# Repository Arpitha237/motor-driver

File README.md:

# Dual DC Motor Driver (L293D) 

Controls two DC motors independently (direction & enable) using an L293D driver IC and a 5V regulated supply.

## Components:

* **U1 (L293D):** Dual H-bridge motor driver IC. This chip contains two independent H-bridge circuits, allowing control of the direction and current flow to two DC motors.
* **U2 (L7805):** 5V voltage regulator. This component takes a higher DC input voltage and provides a stable 5V output to power the L293D's logic and the indicator LED.
* **D1 (LED):** Light Emitting Diode. This visual indicator illuminates when the circuit has a stable 5V power supply.
* **R1 (Resistor):** Current-limiting resistor. This resistor is placed in series with the LED to prevent excessive current flow and potential damage to the LED.
* **J1 (Screw Terminal):** Input connector for the external DC power supply. This is where you connect your power source.
* **J2 (Header):** Connector for control input signals. This header receives signals (typically from a microcontroller) to control the enable and direction of both motors.
* **J3 (Header):** Connector for the first DC motor. Connect the two terminals of your first motor here.
* **J4 (Header):** Connector for the second DC motor. Connect the two terminals of your second motor here.

## Working:

1.  **Power Input:** External DC power is connected to the J1 screw terminal. Ensure correct polarity.
2.  **Voltage Regulation:** The L7805 (U2) steps down and stabilizes the input voltage to a consistent 5V, which is crucial for the proper operation of the L293D and other components.
3.  **Power Indication:** When the 5V regulation is successful, the LED (D1) lights up, indicating that the circuit is powered and ready for motor control.
4.  **Motor Enabling:** To allow a motor to run, a HIGH logic signal (+5V) must be applied to the corresponding enable pin on the J2 header (connected to the EN pins of U1). A LOW signal (0V) on the enable pin will stop the motor.
5.  **Direction Control:** The direction of rotation for each motor is determined by the logic levels applied to the respective direction control pins on the J2 header (connected to the input pins of U1, like 1A, 2A, 3A, 4A). Specific HIGH/LOW combinations on these pins dictate the polarity of the voltage applied across the motor terminals. Consult the L293D datasheet for the exact logic table.
6.  **Motor Driving:** Based on the enable and direction signals received from J2, the L293D (U1) activates its internal H-bridge circuitry to control the flow of current through the motors connected to J3 and J4, causing them to rotate in the desired direction or stop.

## Usage:

1.  Connect your external DC power supply to the J1 screw terminal, paying attention to the positive and negative connections.
2.  Connect your two DC motors to the J3 and J4 headers. The initial direction of rotation might depend on the polarity of the motor connections.
3.  Connect the control output pins of your microcontroller or other control system to the J2 header. Ensure your control signals match the logic levels required by the L293D (typically 0V for LOW and 5V for HIGH).
4.  Control the operation of the motors by manipulating the digital signals sent to the enable and direction control pins on the J2 header. Refer to the L293D datasheet for the specific input logic required to achieve forward, reverse, and brake/coast states for each motor.

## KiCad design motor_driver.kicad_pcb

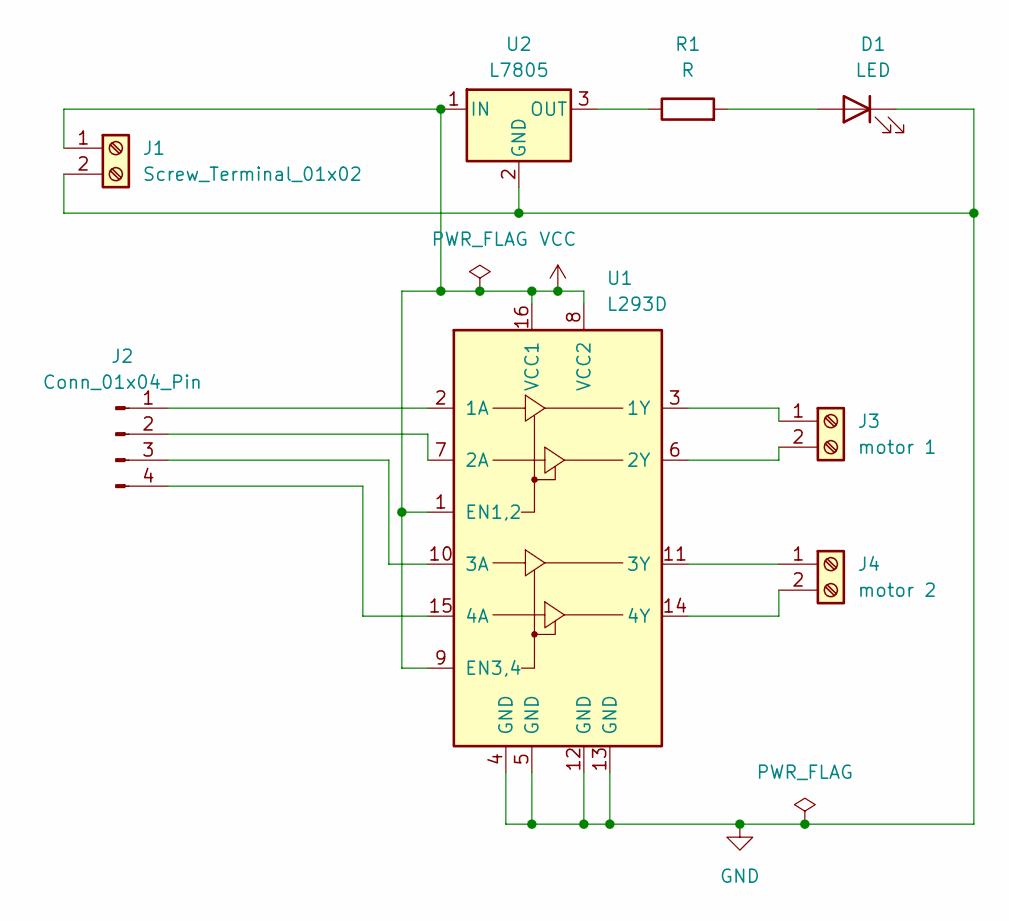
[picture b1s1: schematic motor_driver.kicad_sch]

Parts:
D1: LED; LED_D3.0mm
J1: Screw_Terminal_01x02; TerminalBlock_Phoenix_MKDS-1,5-2-5.08_1x02_P5.08mm_Horizont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
J2: Conn_01x04_Pin; FanPinHeader_1x04_P2.54mm_Vertical
J3: motor 1; TerminalBlock_Phoenix_MKDS-1,5-2-5.08_1x02_P5.08mm_Horizont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
J4: motor 2; TerminalBlock_Phoenix_MKDS-1,5-2-5.08_1x02_P5.08mm_Horizont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
R1: R; R_Axial_DIN0204_L3.6mm_D1.6mm_P7.62mm_Horizontal
U1: L293D; DIP-16_W7.62mm
U2: L7805; TO-220-3_Vertical

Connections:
GND: D1.1 (K), J1.2, U1.4 (GND), U1.5 (GND), U1.12 (GND), U1.13 (GND), U2.2 (GND)
unnamed: D1.2 (A), R1.2
unnamed: J2.1, U1.2 (1A)
unnamed: J2.2, U1.7 (2A)
unnamed: J2.3, U1.10 (3A)
unnamed: J2.4, U1.15 (4A)
unnamed: J3.1, U1.3 (1Y)
unnamed: J3.2, U1.6 (2Y)
unnamed: J4.1, U1.11 (3Y)
unnamed: J4.2, U1.14 (4Y)
unnamed: R1.1, U2.3 (OUT)
VCC: J1.1, U1.1 (EN1,2), U1.8 (VCC2), U1.9 (EN3,4), U1.16 (VCC1), U2.1 (IN)

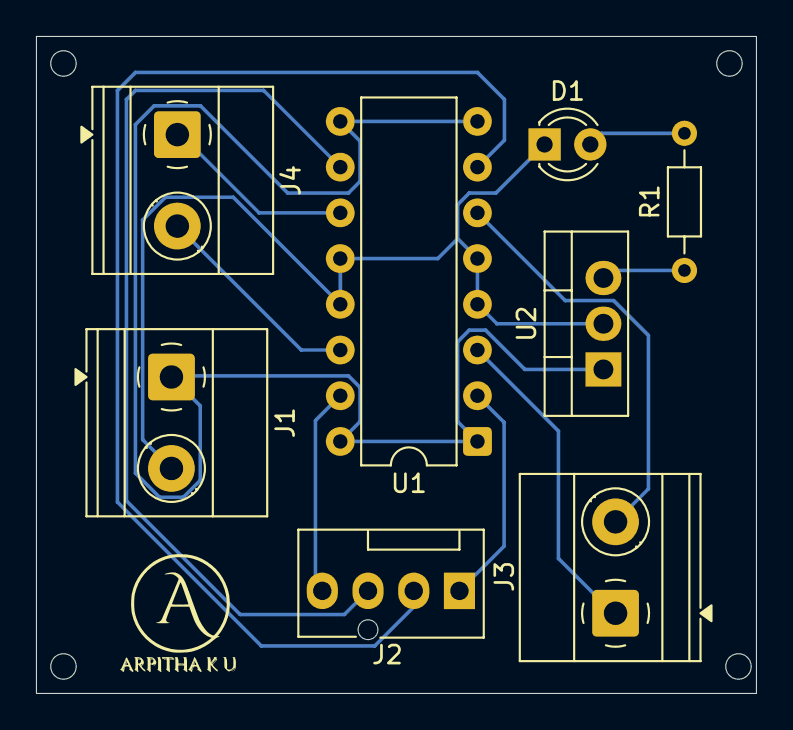
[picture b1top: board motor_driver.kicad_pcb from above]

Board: 2 copper layers, 40.0 x 36.5 mm, 8 parts (0 on the bottom side), 12 nets.

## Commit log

2025-04-28 initial setup
2025-04-28 added components
2025-04-28 designed pcb
